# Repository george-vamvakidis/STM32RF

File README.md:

# STM32RF
STM32 Radio-Frequency Board

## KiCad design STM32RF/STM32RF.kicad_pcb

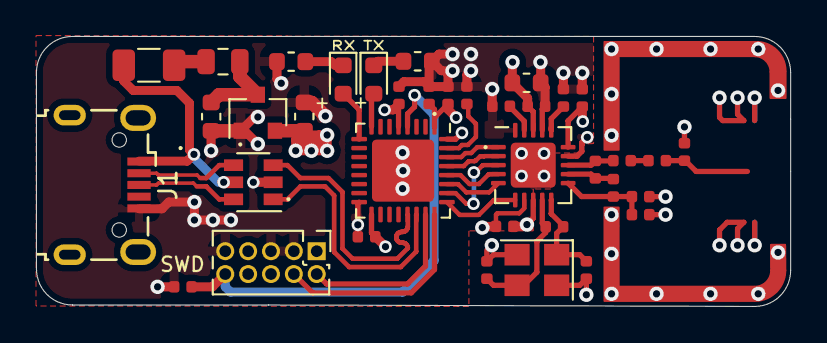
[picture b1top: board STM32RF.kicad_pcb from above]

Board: 2 copper layers, 41.9 x 15.0 mm, 37 parts (0 on the bottom side), 10 nets.

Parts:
C1, C2, C8: 10u; C_0603_1608Metric
C3, C5, C6, C7: 100n; C_0402_1005Metric
C4: 1u; C_0402_1005Metric
C9, C10, C11: 10n; C_0402_1005Metric
C12: 33n; C_0402_1005Metric
C13, C14: 12p; C_0402_1005Metric
C15: 1p5; C_0402_1005Metric
C16: 1p; C_0402_1005Metric
C17: 2n2; C_0402_1005Metric
C18: 4p7; C_0402_1005Metric
D1: GR; LED_0603_1608Metric
D2: YE; LED_0603_1608Metric
F1: 100mA; Fuse_1206_3216Metric
FB1: 100 @ 100MHz; L_0805_2012Metric
J1: USB_B_Micro; USB_Micro-B_Wuerth_629105150521
J3: ARM 10pin; PinHeader_2x05_P1.27mm_Vertical
L1: 3n9; L_0402_1005Metric
L2: 8n2; L_0402_1005Metric
L3: 2n7; L_0402_1005Metric
R1: 2k2; R_0402_1005Metric
R2, R3: 2k2; R_0603_1608Metric
R4: 22k; R_0402_1005Metric
R5: 1M; R_0402_1005Metric
U1: XC6206P332MR; SOT-23
U2: USBLC6-2SC6; SOT-23-6
U3: STM32L432KBU6; QFN-32-1EP_5x5mm_P0.5mm_EP3.45x3.45mm
U4: nRF24L01P; QFN-20-1EP_4x4mm_P0.5mm_EP2.5x2.5mm
Y1: 16MHz; Crystal_SMD_3225-4Pin_3.2x2.5mm

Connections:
+3V3: C2.1, C4.1, C5.1, C6.1, C7.1, C8.1, C9.1, C10.1, C11.1, J3.1, U1.2, U3.1, U3.5, U3.17, U4.7, U4.15, U4.18
+5V: F1.2, J1.1 (VBUS), U2.5
GND: C1.2, C2.2, C3.2, C4.2, C5.2, C6.2, C7.2, C8.2, C9.2, C10.2, C11.2, C12.2, C13.2, C14.2, C16.1, C17.1, C18.1, J1.5 (GND), J3.3, J3.5, J3.9, R1.2, R2.2, R3.2, R4.2, U1.1, U2.2, U3.16, U3.32, U3.33, U4.8, U4.14, U4.17, U4.20, U4.21, Y1.2, Y1.4
unnamed: C1.1, FB1.1, U1.3
unnamed: D1.1, R2.1
unnamed: D1.2, U3.9
unnamed: D2.1, R3.1
unnamed: D2.2, U3.8
unnamed: F1.1, FB1.2
unnamed: R1.1, U3.31
